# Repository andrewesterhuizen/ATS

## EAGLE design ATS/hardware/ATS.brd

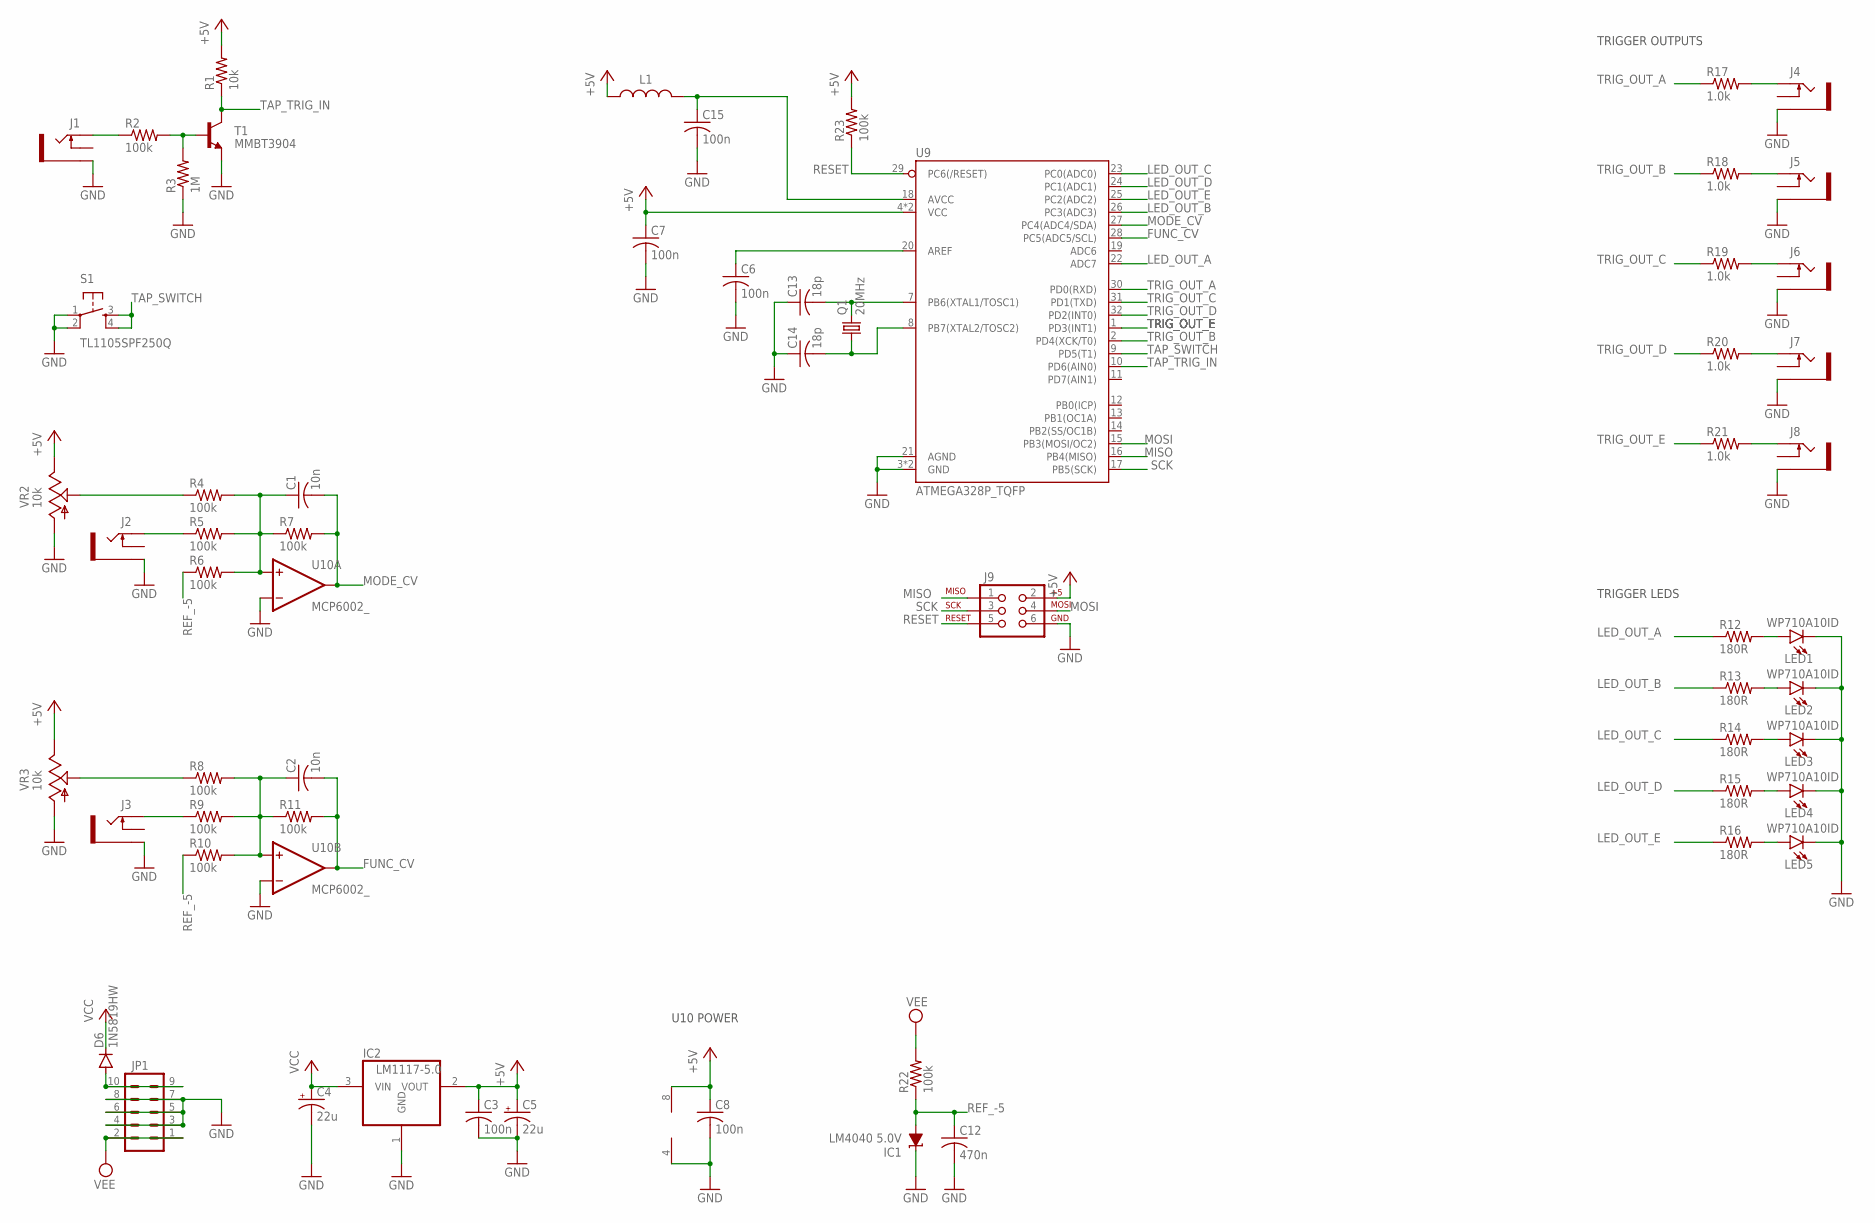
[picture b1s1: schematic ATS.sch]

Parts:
C1, C2: 10n; C0603
C3, C6, C7, C8, C15: 100n; C0603
C4, C5: 22u; PANASONIC_C
C12: 470n; C0603
C13, C14: 18p; C0603
D6: 1N5819HW; SOD123
IC1: LM4040 5.0V; DBZ_R-PDSO-G3
IC2: LM1117-5.0; SOT223
J1, J2, J3, J4, J5, J6, J7, J8: THONKICONNNEW; WQP-PJ301M-12_JACK
J9: AVR_SPI_PRG_6PTH; 2X3
JP1: EURO_POWER_HEADERREGULAR; EURO_POWER_HEADER
L1: 470Ohm@100MHz; WE-CBF_0603(W=2.2)
LED1, LED2, LED3, LED4, LED5: WP710A10ID; LED_3MM
Q1: 20MHz; HC49UP
R1: 10k; R0603
R2, R4, R5, R6, R7, R8, R9, R10, R11, R22, R23: 100k; R0603
R3: 1M; R0603
R12, R13, R14, R15, R16: 180R; R0603
R17, R18, R19, R20, R21: 1.0k; R0603
S1: TL1105SPF250Q; TACTILE-PTH
T1: MMBT3904; SOT23-BEC
U9: ATMEGA328P_TQFP; TQFP32-08
U10: MCP6002_; SO08
VR2, VR3: 10k; 9MM_SNAP-IN_POT

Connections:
+5V: C3.1, C5.+, C7.1, C8.1, IC2.2 (VOUT), J9.2, L1.1, R1.2, R23.2, U9.4 (VCC), U10.8 (V+), VR2.3 (E), VR3.3 (E); also elsewhere on the board
AREF: C6.1, U9.20 (AREF); also elsewhere on the board
FUNC_CV: C2.2, R11.2, U9.28 (PC5(ADC5/SCL)), U10.7 (OUT); also elsewhere on the board
FUNC_JACK: J3.P$1_TIP (TIP), R9.1
FUNC_POT: R8.1, VR3.2 (S); also elsewhere on the board
GND: C3.2, C4.-, C5.-, C6.2, C7.2, C8.2, C12.2, C13.1, C14.1, C15.2, IC1.1 (C), IC2.1 (GND), J1.P$3_SLEEVE (SLEEVE), J2.P$3_SLEEVE (SLEEVE), J3.P$3_SLEEVE (SLEEVE), J4.P$3_SLEEVE (SLEEVE), J5.P$3_SLEEVE (SLEEVE), J6.P$3_SLEEVE (SLEEVE), J7.P$3_SLEEVE (SLEEVE), J8.P$3_SLEEVE (SLEEVE), J9.6, JP1.3, JP1.4, JP1.5, JP1.6, JP1.7, JP1.8, LED1.K (C), LED2.K (C), LED3.K (C), LED4.K (C), LED5.K (C), R3.1, S1.1, S1.2, T1.E, U9.3 (GND), U9.21 (AGND), U10.2 (-IN), U10.4 (V-), U10.6 (-IN), VR2.1 (A), VR3.1 (A); also elsewhere on the board
LED_OUT_A: R12.1, U9.22 (ADC7); also elsewhere on the board
LED_OUT_B: R13.1, U9.26 (PC3(ADC3)); also elsewhere on the board
LED_OUT_C: R14.1, U9.23 (PC0(ADC0)); also elsewhere on the board
LED_OUT_D: R15.1, U9.24 (PC1(ADC1)); also elsewhere on the board
LED_OUT_E: R16.1, U9.25 (PC2(ADC2)); also elsewhere on the board
MISO: J9.1, U9.16 (PB4(MISO)); also elsewhere on the board
MODE_CV: C1.2, R7.2, U9.27 (PC4(ADC4/SDA)), U10.1 (OUT); also elsewhere on the board
MODE_JACK: J2.P$1_TIP (TIP), R5.1
MODE_POT: R4.1, VR2.2 (S); also elsewhere on the board
MOSI: J9.4, U9.15 (PB3(MOSI/OC2)); also elsewhere on the board
unnamed: LED1.A, R12.2
unnamed 17: C1.1, R4.2, R5.2, R6.2, R7.1, U10.3 (+IN); also elsewhere on the board
unnamed 18: C2.1, R8.2, R9.2, R10.2, R11.1, U10.5 (+IN); also elsewhere on the board
unnamed: LED2.A, R13.2
unnamed: LED3.A, R14.2
unnamed: R2.2, R3.2, T1.B
unnamed: J1.P$1_TIP (TIP), R2.1
unnamed: LED4.A, R15.2
unnamed: LED5.A, R16.2
unnamed: J4.P$1_TIP (TIP), R17.2
unnamed: J5.P$1_TIP (TIP), R18.2
unnamed: J6.P$1_TIP (TIP), R19.2
unnamed: J7.P$1_TIP (TIP), R20.2
unnamed: J8.P$1_TIP (TIP), R21.2
unnamed 30: C14.2, Q1.1, U9.8 (PB7(XTAL2/TOSC2)); also elsewhere on the board
unnamed 31: C13.2, Q1.2, U9.7 (PB6(XTAL1/TOSC1)); also elsewhere on the board
unnamed 32: C15.1, L1.2, U9.18 (AVCC); also elsewhere on the board
unnamed: D6.A, JP1.9, JP1.10
REF_-5: C12.1, IC1.2 (A), R6.1, R10.1, R22.1
RESET: J9.5, R23.1, U9.29 (PC6(/RESET)); also elsewhere on the board
SCK: J9.3, U9.17 (PB5(SCK)); also elsewhere on the board
TAP_SWITCH: S1.3, S1.4, U9.9 (PD5(T1)); also elsewhere on the board
TAP_TRIG_IN: R1.1, T1.C, U9.10 (PD6(AIN0)); also elsewhere on the board
TRIG_OUT_A: R17.1, U9.30 (PD0(RXD)); also elsewhere on the board
TRIG_OUT_B: R18.1, U9.2 (PD4(XCK/T0)); also elsewhere on the board
TRIG_OUT_C: R19.1, U9.31 (PD1(TXD)); also elsewhere on the board
TRIG_OUT_D: R20.1, U9.32 (PD2(INT0)); also elsewhere on the board
TRIG_OUT_E: R21.1, U9.1 (PD3(INT1)); also elsewhere on the board
VCC: C4.+, D6.C, IC2.3 (VIN)
VEE: JP1.1, JP1.2, R22.2

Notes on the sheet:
U10 POWER
TRIGGER OUTPUTS
TRIGGER LEDS

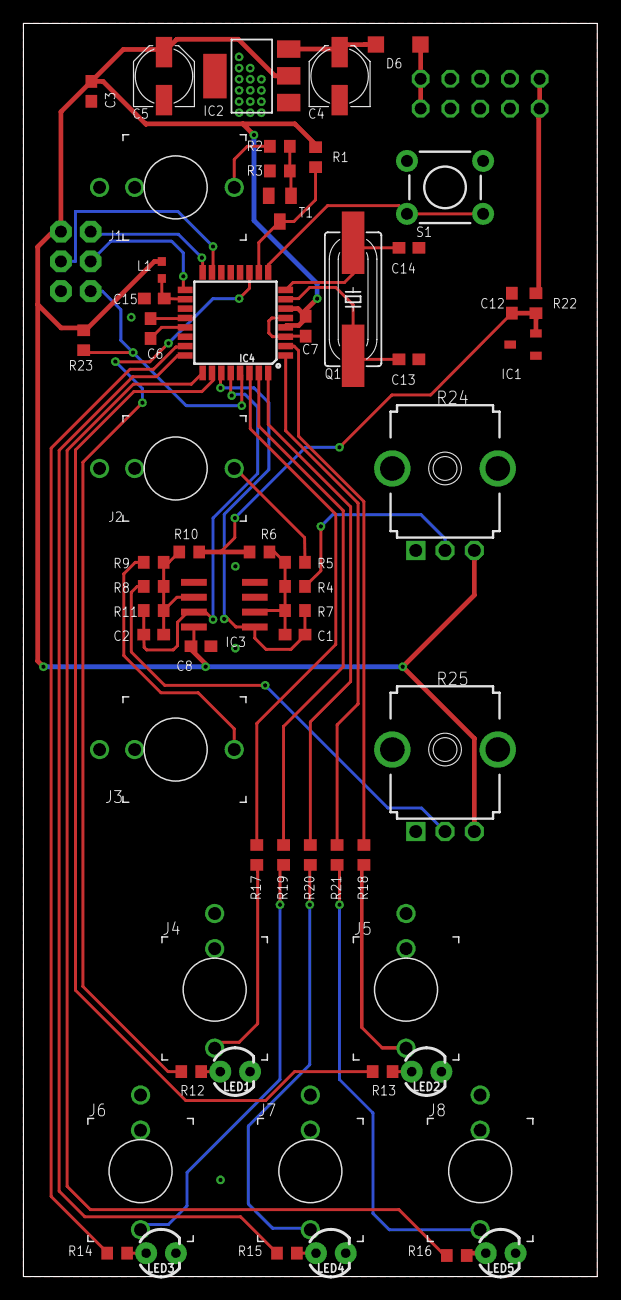
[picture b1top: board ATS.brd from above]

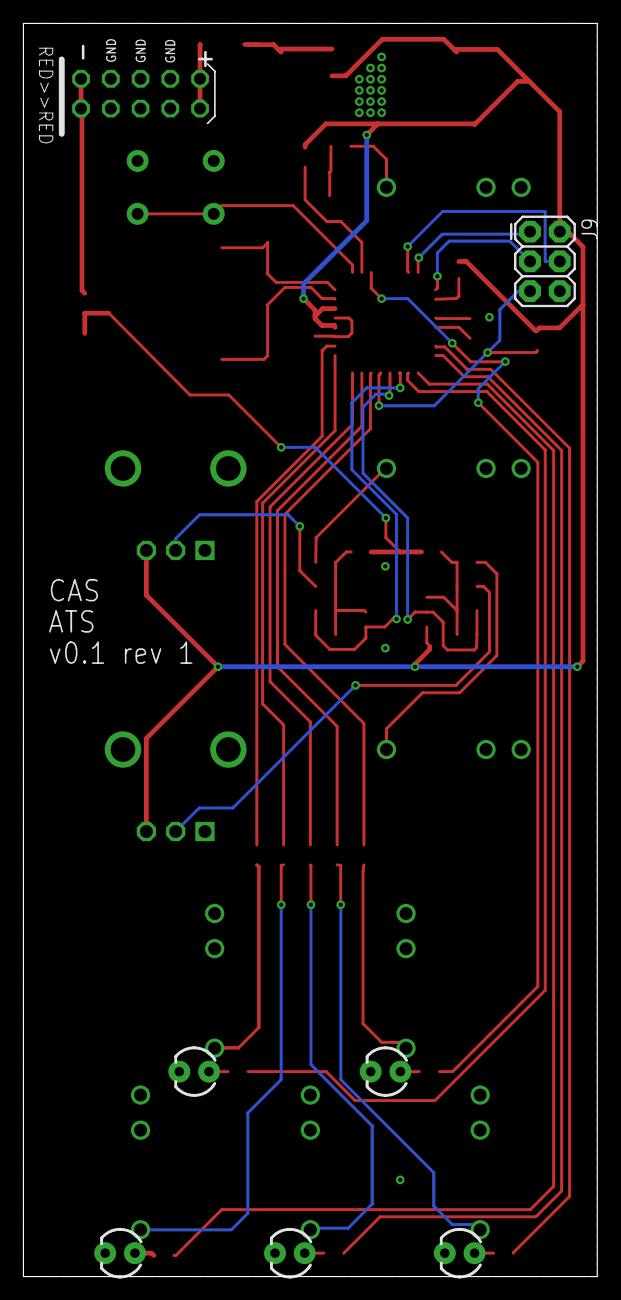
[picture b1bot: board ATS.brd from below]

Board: 2 copper layers, 49.0 x 107.0 mm, 61 parts (2 on the bottom side), 46 nets.

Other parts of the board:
IC3: MCP6002_; SO08
IC4: ATMEGA328P_TQFP; TQFP32-08
R24, R25: 10k; 9MM_SNAP-IN_POT

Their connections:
+5V: IC3.8, IC4.4, IC4.6, R24.3, R25.3; also elsewhere on the board
AREF: IC4.20; also elsewhere on the board
FUNC_CV: IC3.7, IC4.28; also elsewhere on the board
FUNC_POT: R25.2; also elsewhere on the board
GND: IC3.3, IC3.4, IC3.5, IC4.3, IC4.5, IC4.21, R24.1, R25.1; also elsewhere on the board
LED_OUT_A: IC4.11; also elsewhere on the board
LED_OUT_B: IC4.26; also elsewhere on the board
LED_OUT_C: IC4.23; also elsewhere on the board
LED_OUT_D: IC4.24; also elsewhere on the board
LED_OUT_E: IC4.25; also elsewhere on the board
MISO: IC4.16; also elsewhere on the board
MODE_CV: IC3.1, IC4.27; also elsewhere on the board
MODE_POT: R24.2; also elsewhere on the board
MOSI: IC4.15; also elsewhere on the board
unnamed 17: IC3.2; also elsewhere on the board
unnamed 18: IC3.6; also elsewhere on the board
unnamed 30: IC4.8; also elsewhere on the board
unnamed 31: IC4.7; also elsewhere on the board
unnamed 32: IC4.18; also elsewhere on the board
RESET: IC4.29; also elsewhere on the board
SCK: IC4.17; also elsewhere on the board
TAP_SWITCH: IC4.9; also elsewhere on the board
TAP_TRIG_IN: IC4.10; also elsewhere on the board
TRIG_OUT_A: IC4.30; also elsewhere on the board
TRIG_OUT_B: IC4.2; also elsewhere on the board
TRIG_OUT_C: IC4.31; also elsewhere on the board
TRIG_OUT_D: IC4.32; also elsewhere on the board
TRIG_OUT_E: IC4.1; also elsewhere on the board

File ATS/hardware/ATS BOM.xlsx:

QTY | Part | Value | Device | Package
2 | C1,C2 | 10n | C-USC0603 | C0603 | https://www.mouser.co.uk/ProductDetail/KEMET/C0603C103J5RACAUTO
5 | C3,C15,C6,C7,C8 | 100n | C-USC0603 | C0603 | https://www.mouser.co.uk/ProductDetail/80-C0603C104J3RAUTO
1 | C12 | 470n | C-USC0603 | C0603 | https://www.mouser.co.uk/ProductDetail/80-C0603C474Z4VACTU
2 | C13,C14 | 18p | C-USC0603 | C0603 | https://www.mouser.co.uk/ProductDetail/80-C0603X180J5GAUTO
2 | C4,C5 | 22u | CPOL-USC | PANASONIC_C | https://www.mouser.co.uk/ProductDetail/Panasonic/EEE-FP1E220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
5 | R12,R13,R14,R15,R16 | 180R | R-US_R0603 | R0603 | https://www.mouser.co.uk/ProductDetail/Panasonic/ERJ-3EKF180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
5 | R17,R18,R19,R20,R21 | 1.0k | R-US_R0603 | R0603 | https://www.mouser.co.uk/ProductDetail/Panasonic/ERJ-3EKF100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
1 | R1 | 10k | R-US_R0603 | R0603 | https://www.mouser.co.uk/ProductDetail/Panasonic/ERJ-3EKF100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
11 | R2,R4,R5,R6,R7,R8,R9,R10,R11,R22,R23 | 100k | R-US_R0603 | R0603 | https://www.mouser.co.uk/ProductDetail/Panasonic/ERJ-3EKF100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
1 | R3 | 1M | R-US_R0603 | R0603 | https://www.mouser.co.uk/ProductDetail/Panasonic/ERJ-3EKF100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
1 | D6 | 1N5819HW | DIODE-SOD123 | SOD123 | https://www.mouser.co.uk/ProductDetail/Diodes-Incorporated/1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
1 | L1 | 470Ohm@100MHz | WE-CBF_0603_742792642_WB_HS | WE-CBF_0603(W=2.2) | https://www.mouser.co.uk/ProductDetail/Wurth-Elektronik/7427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
1 | T1 | MMBT3904 | MMBT3904LT1-NPN-SOT23-BEC | SOT23-BEC | https://www.mouser.co.uk/ProductDetail/ON-Semiconductor/MMBT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
1 | U10 | MCP6002_ | MCP6002_ | SO08 | https://www.mouser.co.uk/ProductDetail/Microchip-Technology/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
1 | U9 | ATMEGA328P_TQFP | ATMEGA328P_TQFP | TQFP32-08 | https://www.mouser.co.uk/ProductDetail/Microchip-Technology-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
1 | IC1 | LM4040 5.0V | LM4041C12DBZ | DBZ_R-PDSO-G3 | https://www.mouser.co.uk/ProductDetail/Texas-Instruments/LM4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
1 | IC2 | LM1117-5.0 | REG1117 | SOT223 | https://www.mouser.co.uk/ProductDetail/Texas-Instruments/LM1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
8 | J1,J2,J3,J4,J5,J6,J7,J8 | THONKICONNNEW | THONKICONNNEW | WQP-PJ301M-12_JACK | https://www.thonk.co.uk/shop/thonkiconn/
2 | VR2,VR3 | 10k | 9MM_SNAP-IN_POT_ | 9MM_SNAP-IN_POT | https://www.thonk.co.uk/shop/alpha-9mm-pots-dshaft/
5 | LED1,LED2,LED3,LED4,LED5 | WP710A10ID | LED3MM | LED_3MM | https://www.mouser.co.uk/ProductDetail/604-WP710A10ID?R=WP71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
1 | J9 | AVR_SPI_PRG_6PTH | AVR_SPI_PRG_6PTH | 2X3
1 | JP1 | EURO_POWER_HEADERREGULAR | EURO_POWER_HEADERREGULAR | EURO_POWER_HEADER
1 | S1 | TL1105SPF250Q | TAC_SWITCHPTH | TACTILE-PTH | https://www.mouser.co.uk/ProductDetail/E-Switch/TL1105SPF250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 | https://www.mouser.co.uk/ProductDetail/E-Switch/TL1105SPF100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
1 | S1 cap |  |  |  | https://www.mouser.co.uk/ProductDetail/E-Switch/1RBLK?qs=3Jl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

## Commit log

2020-06-14 ATS init
2020-06-15 ATS rev1
2020-07-01 ATS vcv plugin wip
2021-09-08 Updates to UI handling
2021-09-08 Simplify folder structure
2021-09-08 add .DS_Store to .gitignore
2021-09-08 Remove .DS_Store
2021-09-08 Fix casing and make header guards consistent

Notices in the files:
parts and their libraries:
SparkFun-LED: Licensing: Creative Commons ShareAlike 4.0 International - https://creativecommons.org/licenses/by-sa/4.0
SparkFun: Licensing: CC v3.0 Share-Alike You are welcome to use this library for commercial purposes.
Eagle_WE-CBF_rev19b: Copyright: Würth Elektronik
